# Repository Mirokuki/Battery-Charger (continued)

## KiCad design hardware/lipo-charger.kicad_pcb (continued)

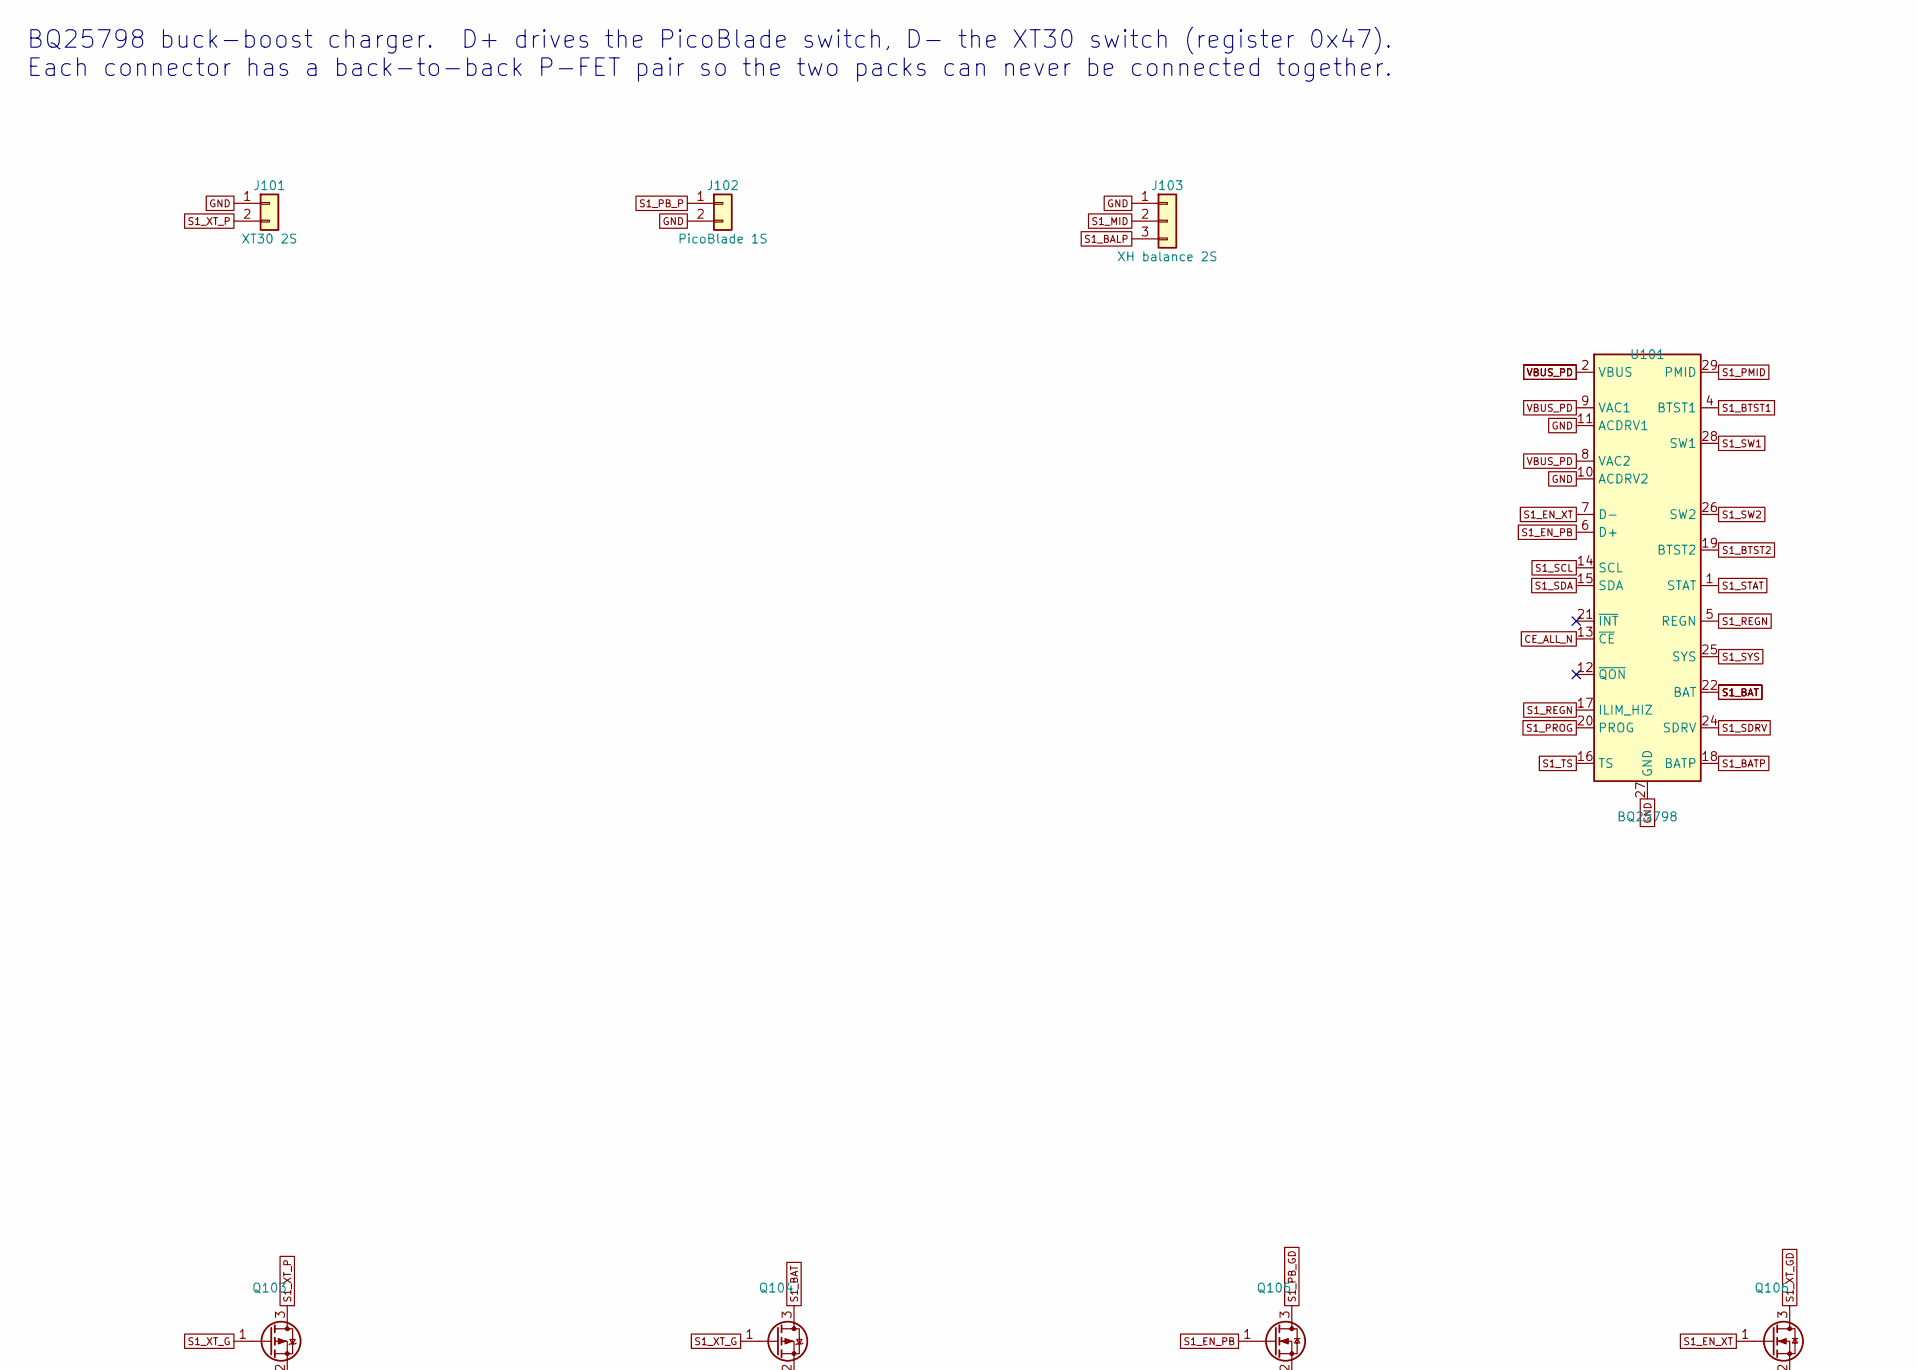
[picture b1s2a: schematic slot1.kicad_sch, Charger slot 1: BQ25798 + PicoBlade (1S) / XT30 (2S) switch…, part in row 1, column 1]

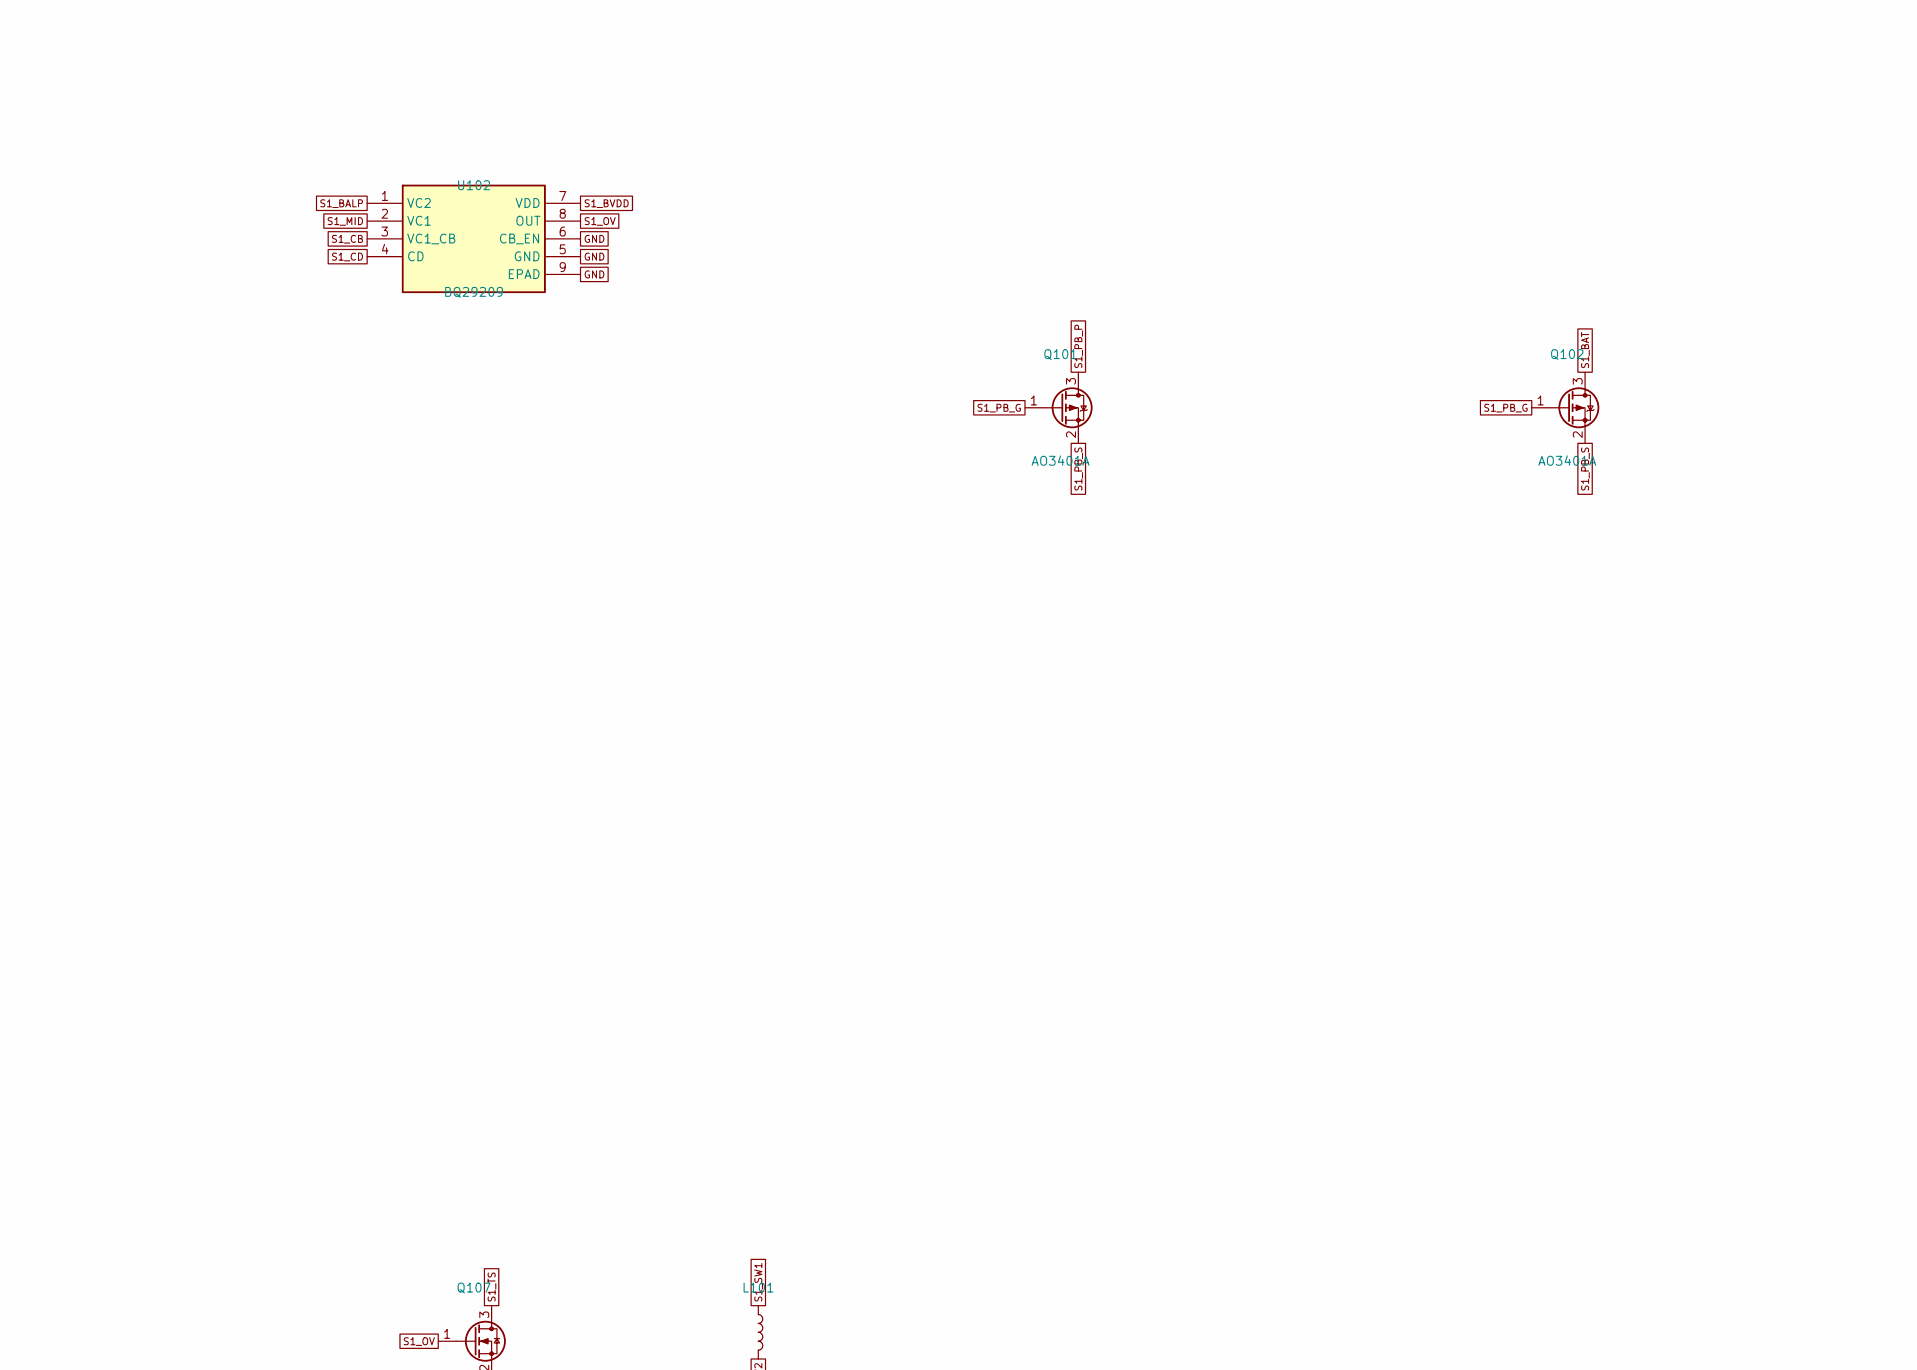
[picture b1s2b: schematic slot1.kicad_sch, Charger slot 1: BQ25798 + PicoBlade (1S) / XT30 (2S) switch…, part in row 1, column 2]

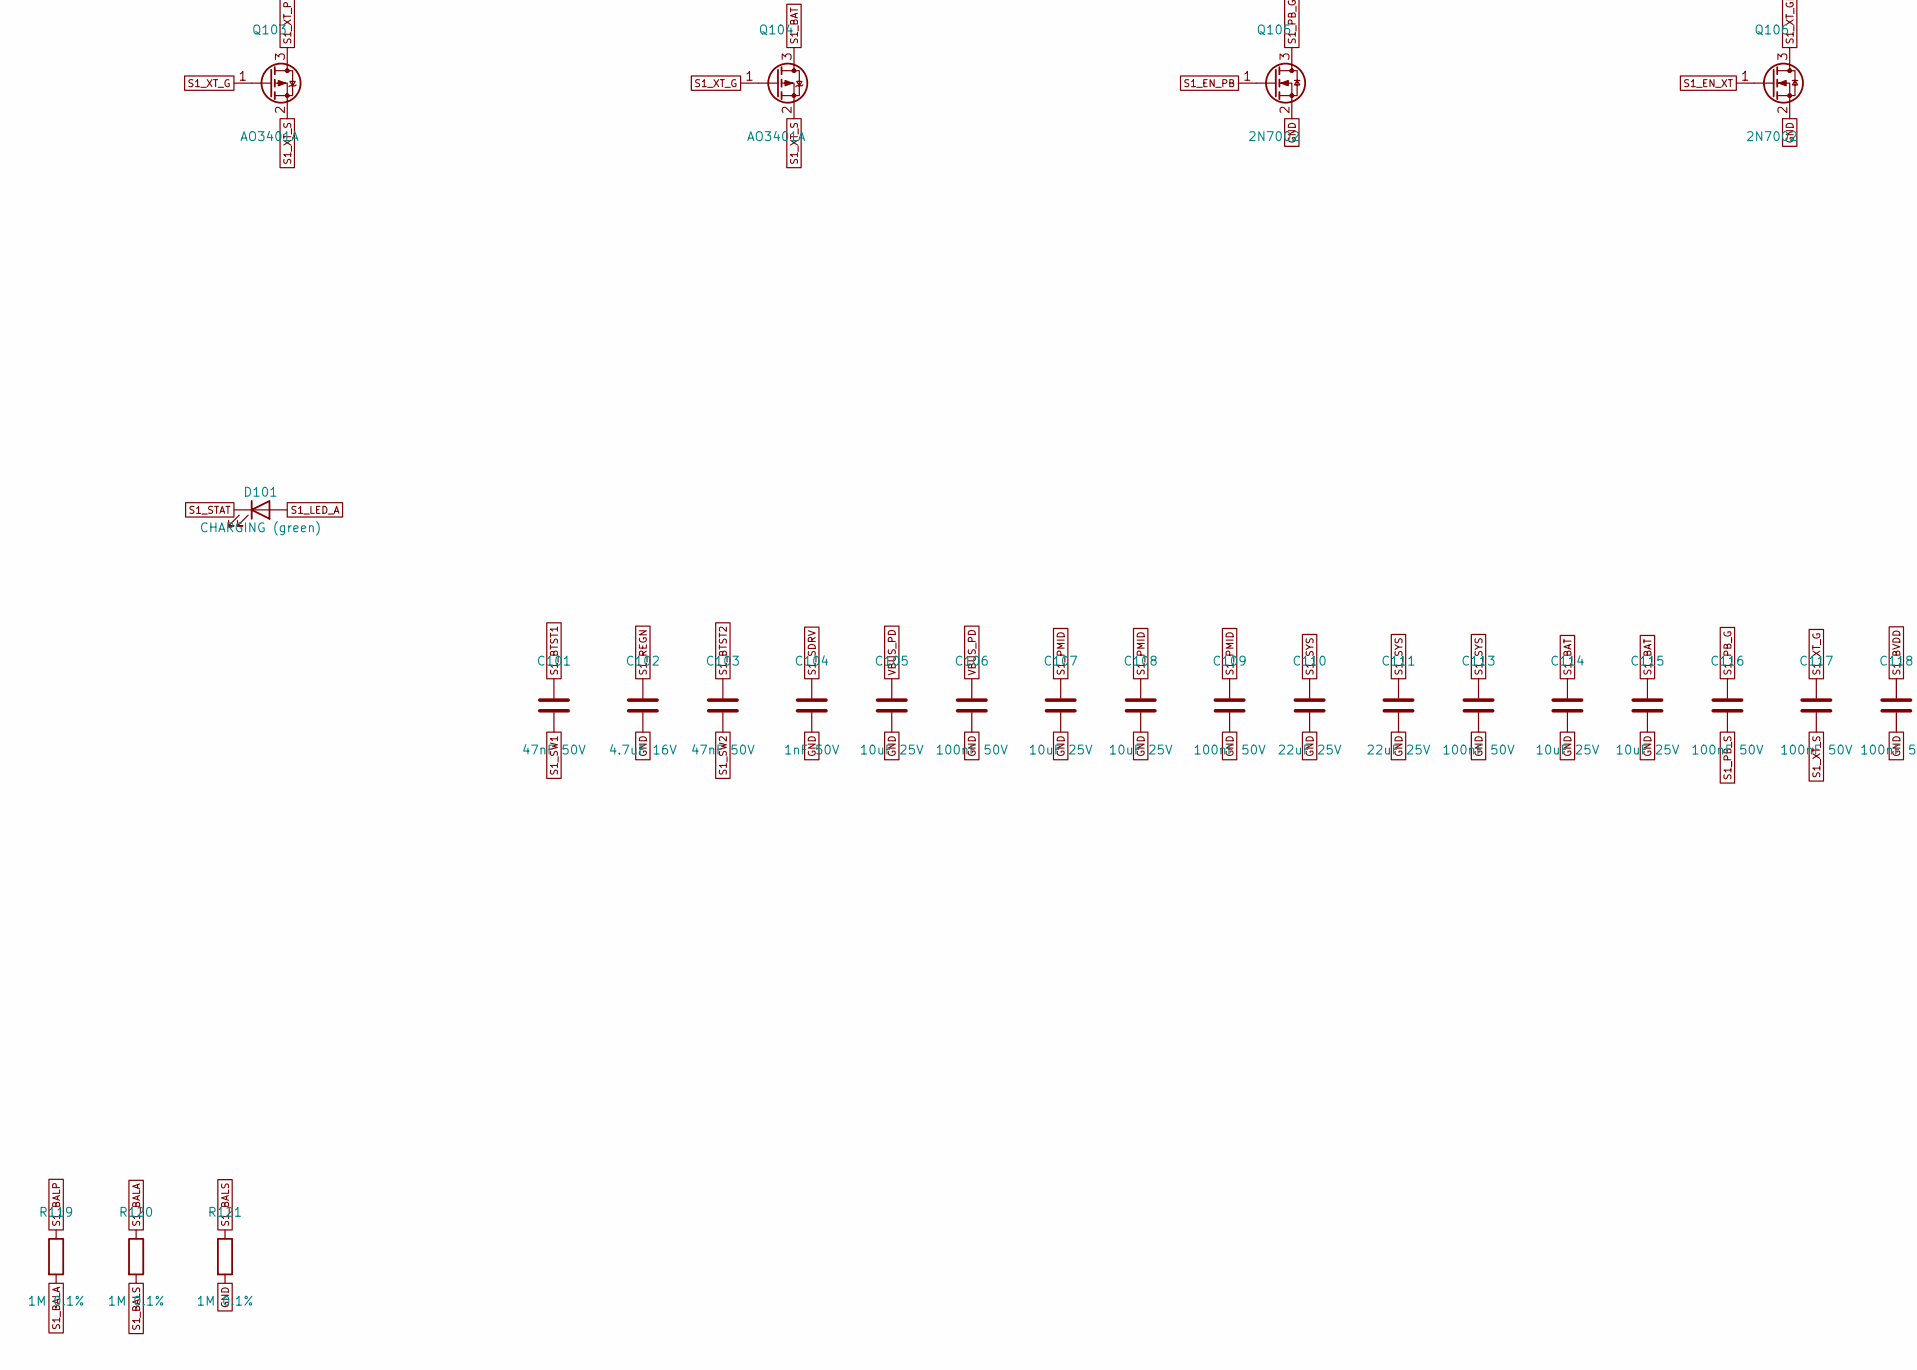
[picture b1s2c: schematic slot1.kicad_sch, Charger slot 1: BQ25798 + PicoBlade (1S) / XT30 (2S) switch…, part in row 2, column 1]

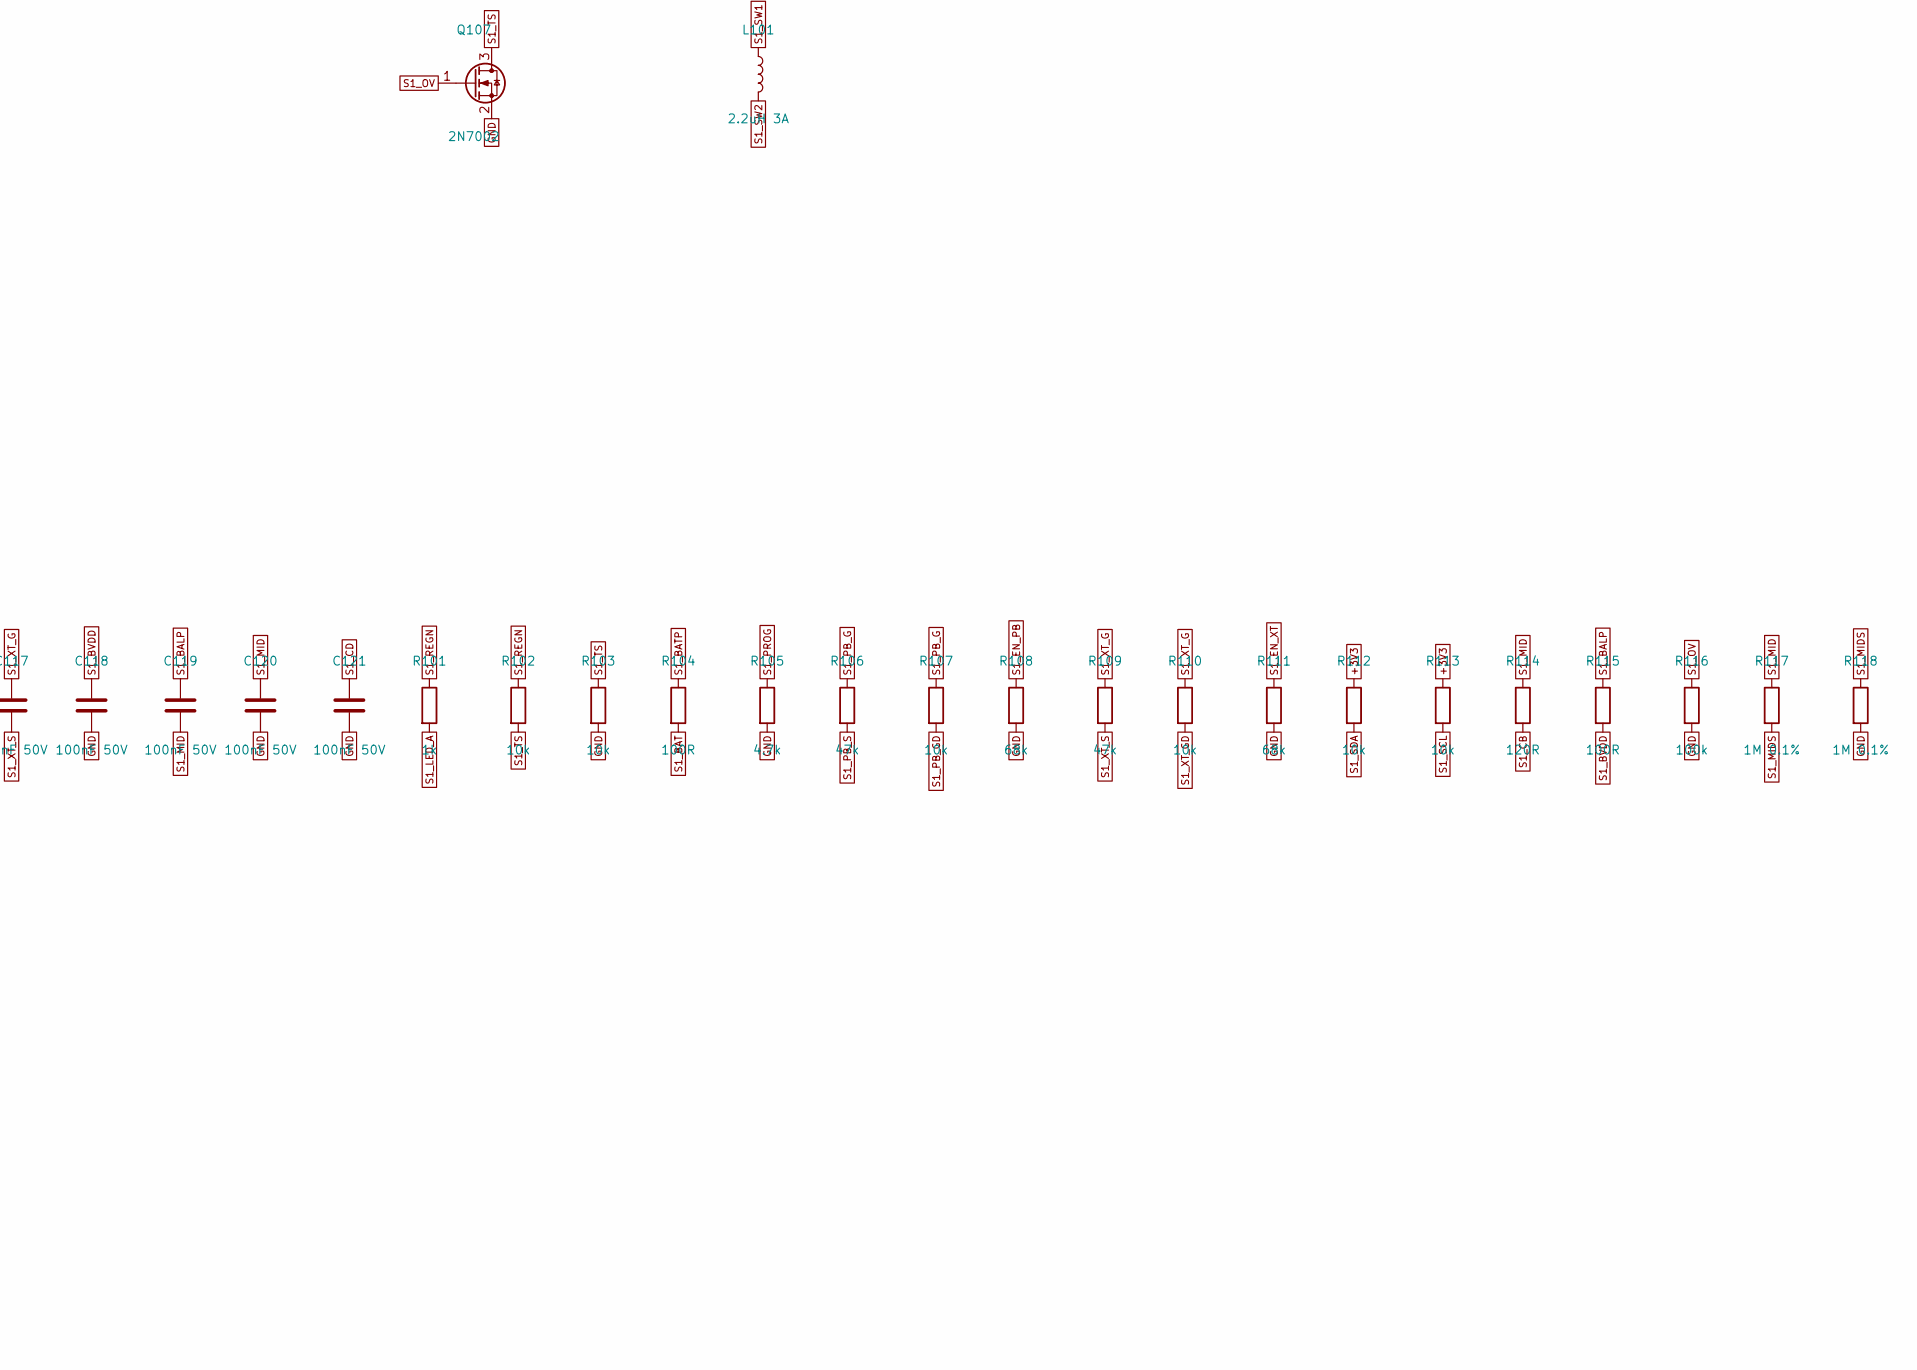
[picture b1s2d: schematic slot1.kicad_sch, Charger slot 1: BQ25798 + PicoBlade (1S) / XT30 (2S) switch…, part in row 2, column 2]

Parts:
C101, C103: 47nF 50V; C_0402_1005Metric; MPN CL05B473KB5NNNC
C102: 4.7uF 16V; C_0603_1608Metric; MPN CL10A475KO8NNNC; LCSC C19666
C104: 1nF 50V; C_0402_1005Metric; MPN CL05B102KB5NNNC; LCSC C1523
C105, C107, C108, C114, C115: 10uF 25V; C_0805_2012Metric; MPN CL21A106KAYNNNE; LCSC C15850
C106, C109, C113, C116, C117, C118, C119, C120, C121: 100nF 50V; C_0402_1005Metric; MPN CL05B104KB54PNC; LCSC C307331
C110, C111: 22uF 25V; C_0805_2012Metric; MPN CL21A226MAQNNNE; LCSC C45783
D101: CHARGING (green); LED_0603_1608Metric; MPN 19-217/GHC-YR1S2/3T; LCSC C72043
J101: XT30 2S; AMASS_XT30UPB-M_1x02_P5.0mm_Vertical; MPN XT30UPB-M; LCSC C99101
J102: PicoBlade 1S; Molex_PicoBlade_53047-0210_1x02_P1.25mm_Vertical; MPN 0530470210
J103: XH balance 2S; JST_XH_B3B-XH-A_1x03_P2.50mm_Vertical; MPN B3B-XH-A; LCSC C144394
L101: 2.2uH 3A; L_Changjiang_FNR4030S; MPN FNR4030S2R2MT
Q101, Q102, Q103, Q104: AO3401A; SOT-23; MPN AO3401A; LCSC C15127
Q105, Q106, Q107: 2N7002; SOT-23; MPN 2N7002; LCSC C8545
R101: 1k; R_0402_1005Metric; MPN 0402WGF1001TCE; LCSC C11702
R102, R103, R107, R110, R112, R113: 10k; R_0402_1005Metric; MPN 0402WGF1002TCE; LCSC C25744
R104, R115: 100R; R_0402_1005Metric; MPN 0402WGF1000TCE; LCSC C25076
R105: 4.7k; R_0402_1005Metric; MPN 0402WGF4701TCE; LCSC C25900
R106, R109: 47k; R_0402_1005Metric; MPN 0402WGF4702TCE; LCSC C25792
R108, R111: 68k; R_0402_1005Metric; MPN 0402WGF6802TCE; LCSC C36871
R114: 120R; R_0402_1005Metric; MPN 0402WGF1200TCE
R116: 100k; R_0402_1005Metric; MPN 0402WGF1003TCE; LCSC C25741
R117, R118, R119, R120, R121: 1M 0.1%; R_0402_1005Metric; MPN RT0402BRD071ML
U101: BQ25798; Texas_RQM0029A_VQFN-29_4x4mm_P0.4mm; MPN BQ25798RQMR; LCSC C2876768
U102: BQ29209; VSON-8-1EP_3x3mm_P0.65mm_EP1.65x2.4mm; MPN BQ29209DRBR

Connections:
+3V3: R112.1, R113.1; also elsewhere on the board
CE_ALL_N: U101.13 (~CE); also elsewhere on the board
GND: C102.2, C104.2, C105.2, C106.2, C107.2, C108.2, C109.2, C110.2, C111.2, C113.2, C114.2, C115.2, C118.2, C120.2, C121.2, J101.1, J102.2, J103.1, Q105.2 (S), Q106.2 (S), Q107.2 (S), R103.2, R105.2, R108.2, R111.2, R116.2, R118.2, R121.2, U101.10 (ACDRV2), U101.11 (ACDRV1), U101.27 (GND), U102.5 (GND), U102.6 (CB_EN), U102.9 (EPAD); also elsewhere on the board
S1_BALA: R119.2, R120.1
S1_BALP: C119.1, J103.3, R115.1, R119.1, U102.1 (VC2)
S1_BALS: R120.2, R121.1; also elsewhere on the board
S1_BAT: C114.1, C115.1, Q102.3 (D), Q104.3 (D), R104.2, U101.22 (BAT), U101.23 (BAT)
S1_BATP: R104.1, U101.18 (BATP)
S1_BTST1: C101.1, U101.4 (BTST1)
S1_BTST2: C103.1, U101.19 (BTST2)
S1_BVDD: C118.1, R115.2, U102.7 (VDD)
S1_CB: R114.2, U102.3 (VC1_CB)
S1_CD: C121.1, U102.4 (CD)
S1_EN_PB: Q105.1 (G), R108.1, U101.6 (D+)
S1_EN_XT: Q106.1 (G), R111.1, U101.7 (D-)
S1_LED_A: D101.2 (A), R101.2
S1_MID: C119.2, C120.1, J103.2, R114.1, R117.1, U102.2 (VC1)
S1_MIDS: R117.2, R118.1; also elsewhere on the board
S1_OV: Q107.1 (G), R116.1, U102.8 (OUT)
S1_PB_G: C116.1, Q101.1 (G), Q102.1 (G), R106.1, R107.1
S1_PB_GD: Q105.3 (D), R107.2
S1_PB_P: J102.1, Q101.3 (D)
S1_PB_S: C116.2, Q101.2 (S), Q102.2 (S), R106.2
S1_PMID: C107.1, C108.1, C109.1, U101.29 (PMID)
S1_PROG: R105.1, U101.20 (PROG)
S1_REGN: C102.1, R101.1, R102.1, U101.5 (REGN), U101.17 (ILIM_HIZ)
S1_SCL: R113.2, U101.14 (SCL); also elsewhere on the board
S1_SDA: R112.2, U101.15 (SDA); also elsewhere on the board
S1_SDRV: C104.1, U101.24 (SDRV)
S1_STAT: D101.1 (K), U101.1 (STAT)
S1_SW1: C101.2, L101.1, U101.28 (SW1)
S1_SW2: C103.2, L101.2, U101.26 (SW2)
S1_SYS: C110.1, C111.1, C113.1, U101.25 (SYS)
S1_TS: Q107.3 (D), R102.2, R103.1, U101.16 (TS)
S1_XT_G: C117.1, Q103.1 (G), Q104.1 (G), R109.1, R110.1
S1_XT_GD: Q106.3 (D), R110.2
S1_XT_P: J101.2, Q103.3 (D)
S1_XT_S: C117.2, Q103.2 (S), Q104.2 (S), R109.2
VBUS_PD: C105.1, C106.1, U101.2 (VBUS), U101.3 (VBUS), U101.8 (VAC2), U101.9 (VAC1); also elsewhere on the board

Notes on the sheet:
BQ25798 buck-boost charger. D+ drives the PicoBlade switch, D- the XT30 switch (register 0x47). Each connector has a back-to-back P-FET pair so the two packs can never be connected together.
